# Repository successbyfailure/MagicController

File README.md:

# Magic Controller
wide range wled controllers

## Cargador de librerias
Carga las referencias LCSC de un csv con campo LCSC y descarga con easyeda2kicad todas las librerias en easyeda-libs
  
  python3 easyeda2kicad_from_csv.py componentes.csv

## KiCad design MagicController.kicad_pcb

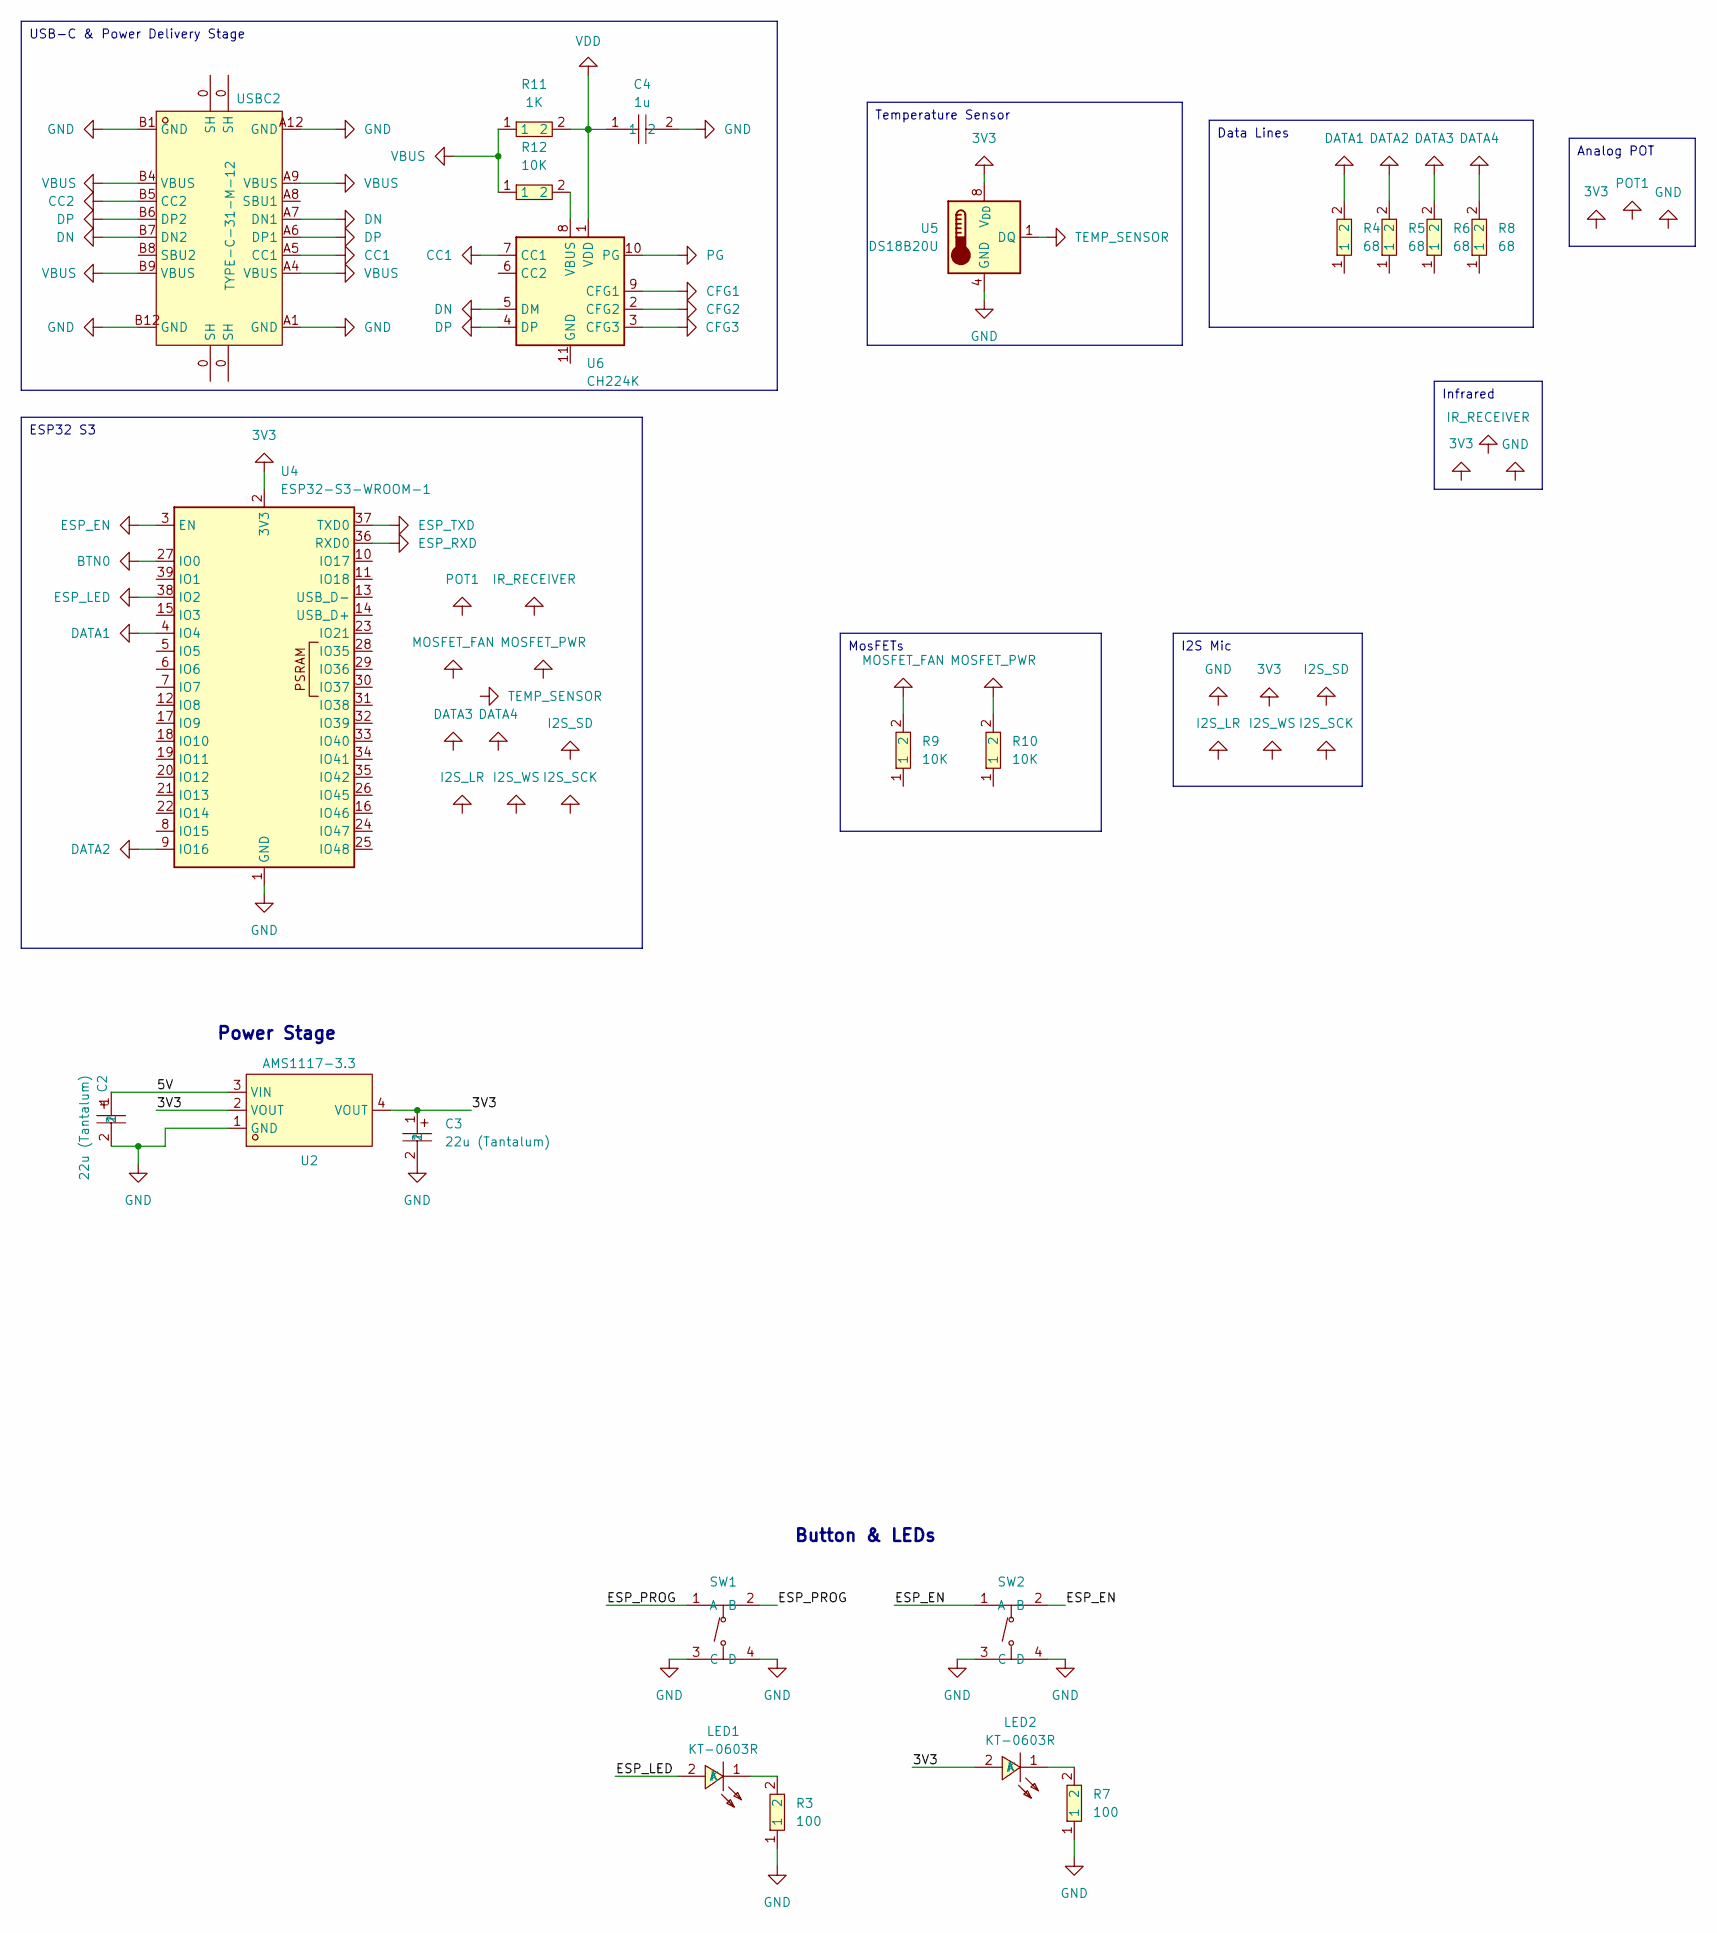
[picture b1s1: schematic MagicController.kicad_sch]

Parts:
C2, C3: 22u (Tantalum); CASE-A_3216; LCSC Part C129272
C4: 1u; C0603; LCSC Part C14663
LED1, LED2: KT-0603R; LED0603-RD; LCSC Part C2286
R3, R7: 100; R0603; LCSC Part C22775
R4, R5, R6, R8: 68; R0603; LCSC Part C22775
R9, R10, R12: 10K; R0603; LCSC Part C22775
R11: 1K; R0603; LCSC Part C22775
SW1, SW2: TS-1187A-B-A-B; SW-SMD_4P-L5.1-W5.1-P3.70-LS6.5-TL_H1.5; LCSC Part C318884
U2: AMS1117-3.3; SOT-223-3_L6.5-W3.4-P2.30-LS7.0-BR; LCSC Part C6186
U4: ESP32-S3-WROOM-1; ESP32-S3-WROOM-2
U5: DS18B20U; MSOP-8_3x3mm_P0.65mm
U6: CH224K; SSOP-10-1EP_3.9x4.9mm_P1mm_EP2.1x3.3mm_ThermalVias
USBC2: TYPE-C-31-M-12; USB-C_SMD-TYPE-C-31-M-12; LCSC Part C165948

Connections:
3V3: C3.1, LED2.2 (A), U2.2 (VOUT), U2.4 (VOUT), U4.2 (3V3), U5.8 (V_{DD})
/5V: C2.1, U2.3 (VIN)
/ESP_PROG: SW1.1 (A), SW1.2 (B)
BTN0: U4.27 (IO0)
CC1: U6.7 (CC1), USBC2.A5 (CC1)
CC2: USBC2.B5 (CC2)
CFG1: U6.9 (CFG1)
CFG2: U6.2 (CFG2)
CFG3: U6.3 (CFG3)
DATA1: R4.2, U4.4 (IO4)
DATA2: R5.2, U4.9 (IO16)
DATA3: R6.2
DATA4: R8.2
DN: U6.5 (DM), USBC2.A7 (DN1), USBC2.B7 (DN2)
DP: U6.4 (DP), USBC2.A6 (DP1), USBC2.B6 (DP2)
ESP_EN: SW2.1 (A), SW2.2 (B), U4.3 (EN)
ESP_LED: LED1.2 (A), U4.38 (IO2)
ESP_RXD: U4.36 (RXD0)
ESP_TXD: U4.37 (TXD0)
GND: C2.2, C3.2, C4.2, R3.1, R7.1, SW1.3 (C), SW1.4 (D), SW2.3 (C), SW2.4 (D), U2.1 (GND), U4.1 (GND), U4.40 (GND), U4.41 (GND), U5.4 (GND), USBC2.A1 (GND), USBC2.A12 (GND), USBC2.B1 (GND), USBC2.B12 (GND)
MOSFET_FAN: R9.2
MOSFET_PWR: R10.2
unnamed: LED1.1 (K), R3.2
unnamed: LED2.1 (K), R7.2
unnamed: R12.2, U6.8 (VBUS)
PG: U6.10 (PG)
TEMP_SENSOR: U5.1 (DQ)
VBUS: R11.1, R12.1, USBC2.A4 (VBUS), USBC2.A9 (VBUS), USBC2.B4 (VBUS), USBC2.B9 (VBUS)
VDD: C4.1, R11.2, U6.1 (VDD)

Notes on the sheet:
ESP32 S3
Analog POT
I2S Mic
MosFETs
Infrared
Temperature Sensor
Data Lines
USB-C & Power Delivery Stage
Power Stage
Button & LEDs

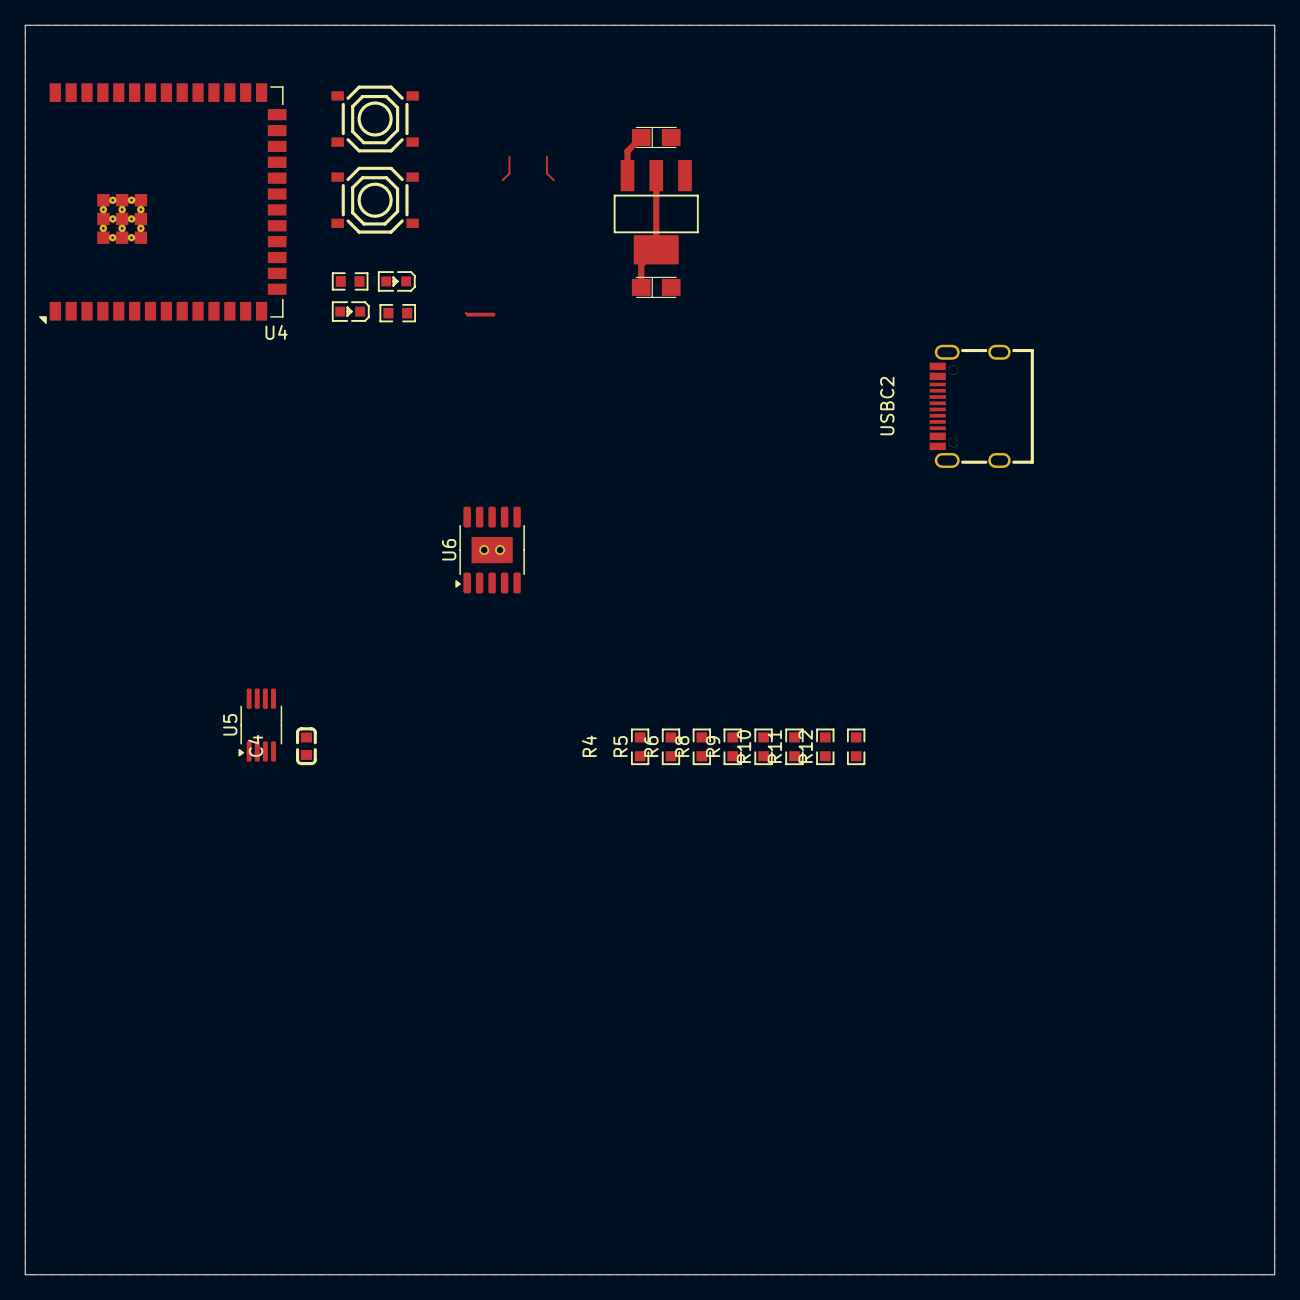
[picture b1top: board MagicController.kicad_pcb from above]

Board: 2 copper layers, 100.0 x 100.0 mm, 22 parts (0 on the bottom side), 16 nets.

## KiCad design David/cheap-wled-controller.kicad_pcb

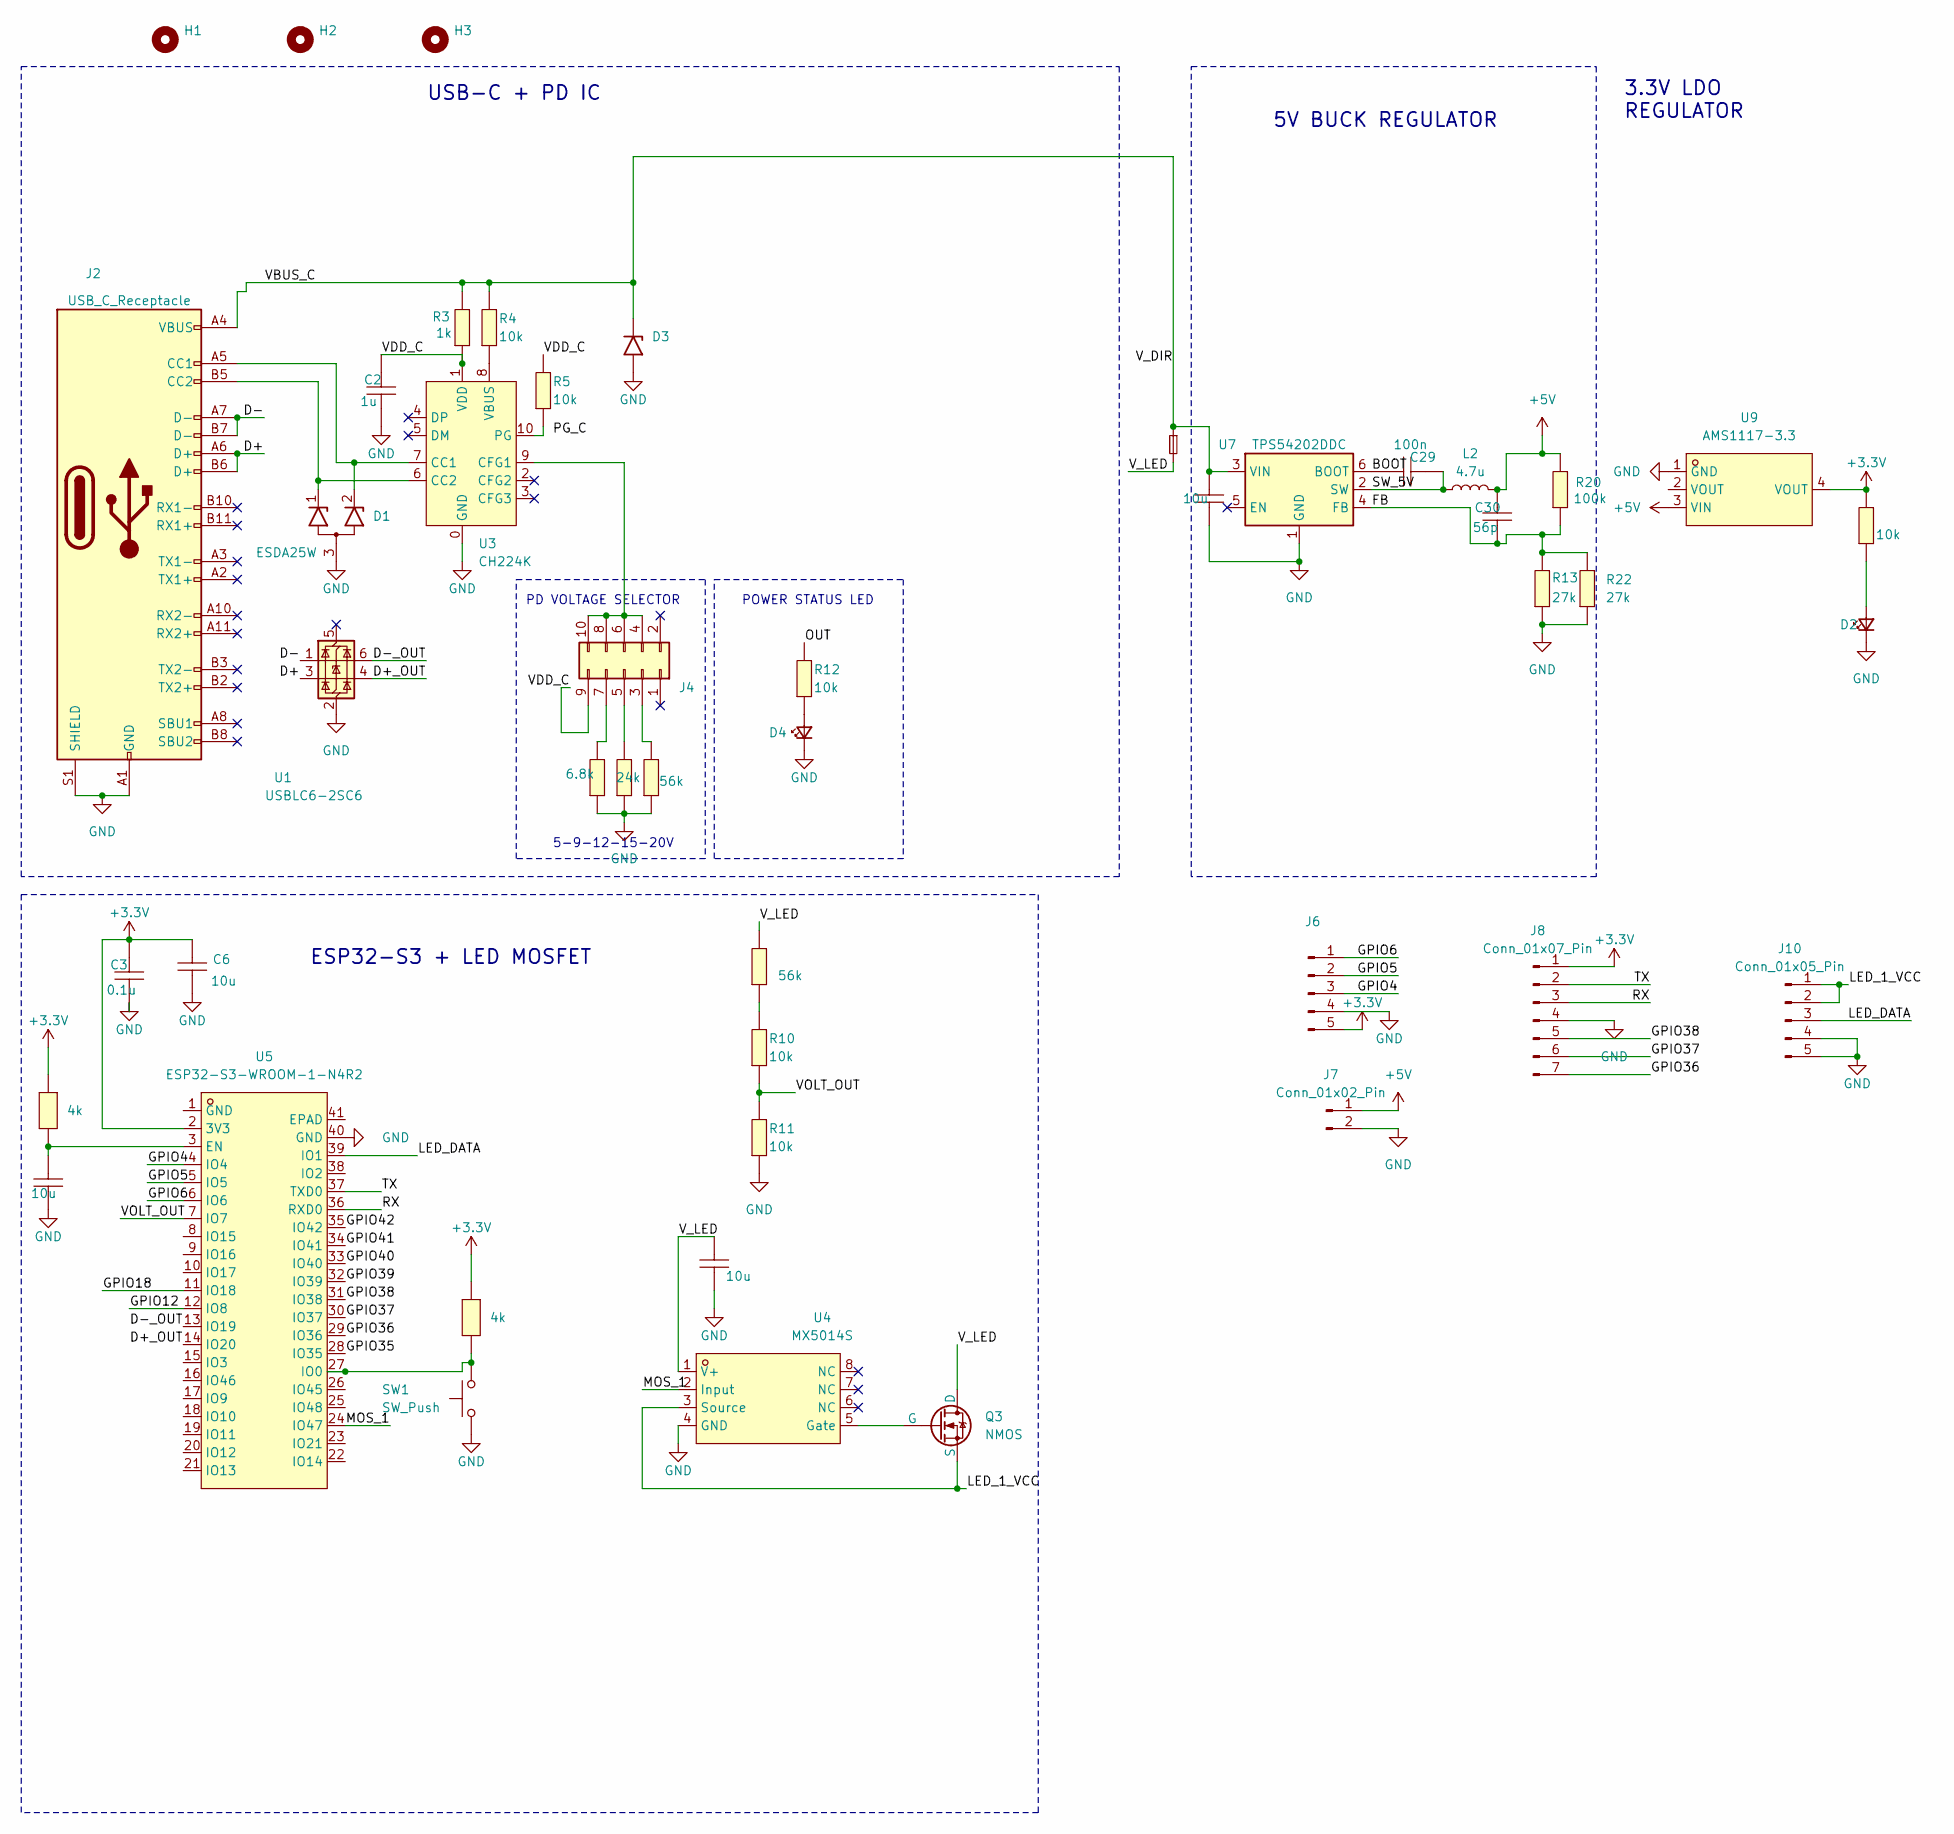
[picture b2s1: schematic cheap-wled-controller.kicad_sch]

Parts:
C1, C5, C6, C7: 10u; C0805; LCSC Part C1713
C2: 1u; C0805; LCSC Part C215803
C3: 0.1u; C0805; LCSC Part C476766
C29: 100n; C0805; LCSC Part C476766
C30: 56p; C0805; LCSC Part C1828
D1: ESDA25W; SOT-323_SC-70; LCSC C3021136
D2: LED_Small; LED0805-R-RD; LCSC C5123548
D3: D_SMA; LCSC C383698
D4: LED_Small; LED0805-R-RD; LCSC C965799
F2: DIR; FUSE-TH_XF-508P-A-B; LCSC C19727304
H1, H2, H3: MountingHole_3.2mm_M3
J2: USB_C_Receptacle; USB-C_SMD-TYPE-C-31-M-12; LCSC C165948
J4: Conn_02x05_Odd_Even; PinHeader_2x05_P2.00mm_Vertical; LCSC C7501288
J6: Conn_01x05_Pin; PinSocket_1x05_P2.54mm_Vertical
J7: Conn_01x02_Pin; JST_PH_B2B-PH-K_1x02_P2.00mm_Vertical; LCSC C131337
J8: Conn_01x07_Pin; PinSocket_1x07_P2.54mm_Vertical
J10: Conn_01x05_Pin; CONN-TH_5P-P3.81_KF124-3.81-5P; LCSC C72336
L2: 4.7u; L_1008_2520Metric; LCSC C91237
Q3: NMOS; DFN-8_L5.9-W5.2-P1.27-LS6.2-BL; LCSC C919580
R2, R15: 56k; R0805; LCSC Part C17756
R3: 1k; R0805; LCSC Part C17513
R4, R5, R10, R11, R12, R14: 10k; R0805; LCSC Part C17414
R6, R7: 4k; R0805; LCSC Part C2828855
R13, R22: 27k; R0805; LCSC Part C114533
R16: 24k; R0805; LCSC Part C17575
R17: 6.8k; R0805; LCSC Part C17772
R20: 100k; R0805; LCSC Part C149504
SW1: SW_Push; SW-SMD_TSA245G00D-250; LCSC C2846758
U1: USBLC6-2SC6; SOT-23-6; LCSC C2827654
U3: CH224K; ESSOP-10_L4.9-W3.9-P1.0-LS6.0-TL-EP; LCSC C970725
U4: MX5014S; SOIC-8_L4.9-W3.9-P1.27-LS6.0-BL; LCSC Part C5359091
U5: ESP32-S3-WROOM-1-N4R2; WIRELM-SMD_ESP32-S3-WROOM-1; LCSC Part C2913203
U7: TPS54202DDC; SOT-23-6; LCSC C191884
U9: AMS1117-3.3; SOT-223-3_L6.5-W3.4-P2.30-LS7.0-BR; LCSC Part C6186

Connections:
+3.3V: C3.2, C6.2, J6.5, J8.1, R6.1, R7.1, R14.2, U5.2 (3V3), U9.4 (VOUT)
+5V: C30.2, J7.1, L2.2, R20.2, U9.3 (VIN)
/BOOT: C29.2, U7.6 (BOOT)
/D+: J2.A6 (D+), J2.B6 (D+), U1.3 (I/O2)
/D+_OUT: U1.4 (I/O2), U5.14 (IO20)
/D-: J2.A7 (D-), J2.B7 (D-), U1.1 (I/O1)
/D-_OUT: U1.6 (I/O1), U5.13 (IO19)
/FB: C30.1, R13.2, R20.1, R22.2, U7.4 (FB)
/GPIO4: J6.3, U5.4 (IO4)
/GPIO5: J6.2, U5.5 (IO5)
/GPIO6: J6.1, U5.6 (IO6)
/GPIO12: U5.12 (IO8)
/GPIO18: U5.11 (IO18)
/GPIO35: U5.28 (IO35)
/GPIO36: J8.7, U5.29 (IO36)
/GPIO37: J8.6, U5.30 (IO37)
/GPIO38: J8.5, U5.31 (IO38)
/GPIO39: U5.32 (IO39)
/GPIO40: U5.33 (IO40)
/GPIO41: U5.34 (IO41)
/GPIO42: U5.35 (IO42)
/LED_1_VCC: J10.1, J10.2, Q3.3 (S), U4.3 (Source)
/LED_DATA: J10.3, U5.39 (IO1)
/MOS_1: U4.2 (Input), U5.24 (IO47)
/OUT: R12.2
/RX: J8.3, U5.36 (RXD0)
/SW_5V: C29.1, L2.1, U7.2 (SW)
/TX: J8.2, U5.37 (TXD0)
/VBUS_C: C5.2, D3.1 (A1), F2.1, J2.A4 (VBUS), J2.A9 (VBUS), J2.B4 (VBUS), J2.B9 (VBUS), R3.2, R4.2, U7.3 (VIN)
/VDD_C: C2.2, J4.9, R3.1, R5.2, U3.1 (VDD)
/VOLT_OUT: R10.1, R11.2, U5.7 (IO7)
/V_LED: C1.2, F2.2, Q3.2 (D), R15.2, U4.1 (V+)
GND: C1.1, C2.1, C3.1, C5.1, C6.1, C7.1, D1.3 (A), D2.1 (K), D3.2 (A2), D4.1 (K), J2.A1 (GND), J2.A12 (GND), J2.B1 (GND), J2.B12 (GND), J2.S1 (SHIELD), J6.4, J7.2, J8.4, J10.4, J10.5, R2.1, R11.1, R13.1, R16.1, R17.1, R22.1, SW1.1, U1.2 (GND), U3.0 (GND), U4.4 (GND), U5.40 (GND), U7.1 (GND), U9.1 (GND)
unnamed: D1.1 (K1), J2.B5 (CC2), U3.6 (CC2)
unnamed: D1.2 (K2), J2.A5 (CC1), U3.7 (CC1)
unnamed: D2.2 (A), R14.1
unnamed: D4.2 (A), R12.1
unnamed: J4.3, R2.2
unnamed: J4.5, R16.2
unnamed: J4.7, R17.2
unnamed: J4.4, J4.6, J4.8, J4.10, U3.9 (CFG1)
unnamed: Q3.1 (G), U4.5 (Gate)
unnamed: R10.2, R15.1
unnamed: R5.1, U3.10 (PG)
unnamed: R4.1, U3.8 (VBUS)
unnamed: C7.2, R6.2, U5.3 (EN)
unnamed: R7.2, SW1.2, U5.27 (IO0)

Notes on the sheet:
ESP32-S3 + LED MOSFET
USB-C + PD IC
POWER STATUS LED
5V BUCK REGULATOR
5-9-12-15-20V
PD VOLTAGE SELECTOR
3.3V LDO REGULATOR

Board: 2 copper layers, 47 parts (1 on the bottom side), 39 nets, no tracks yet.

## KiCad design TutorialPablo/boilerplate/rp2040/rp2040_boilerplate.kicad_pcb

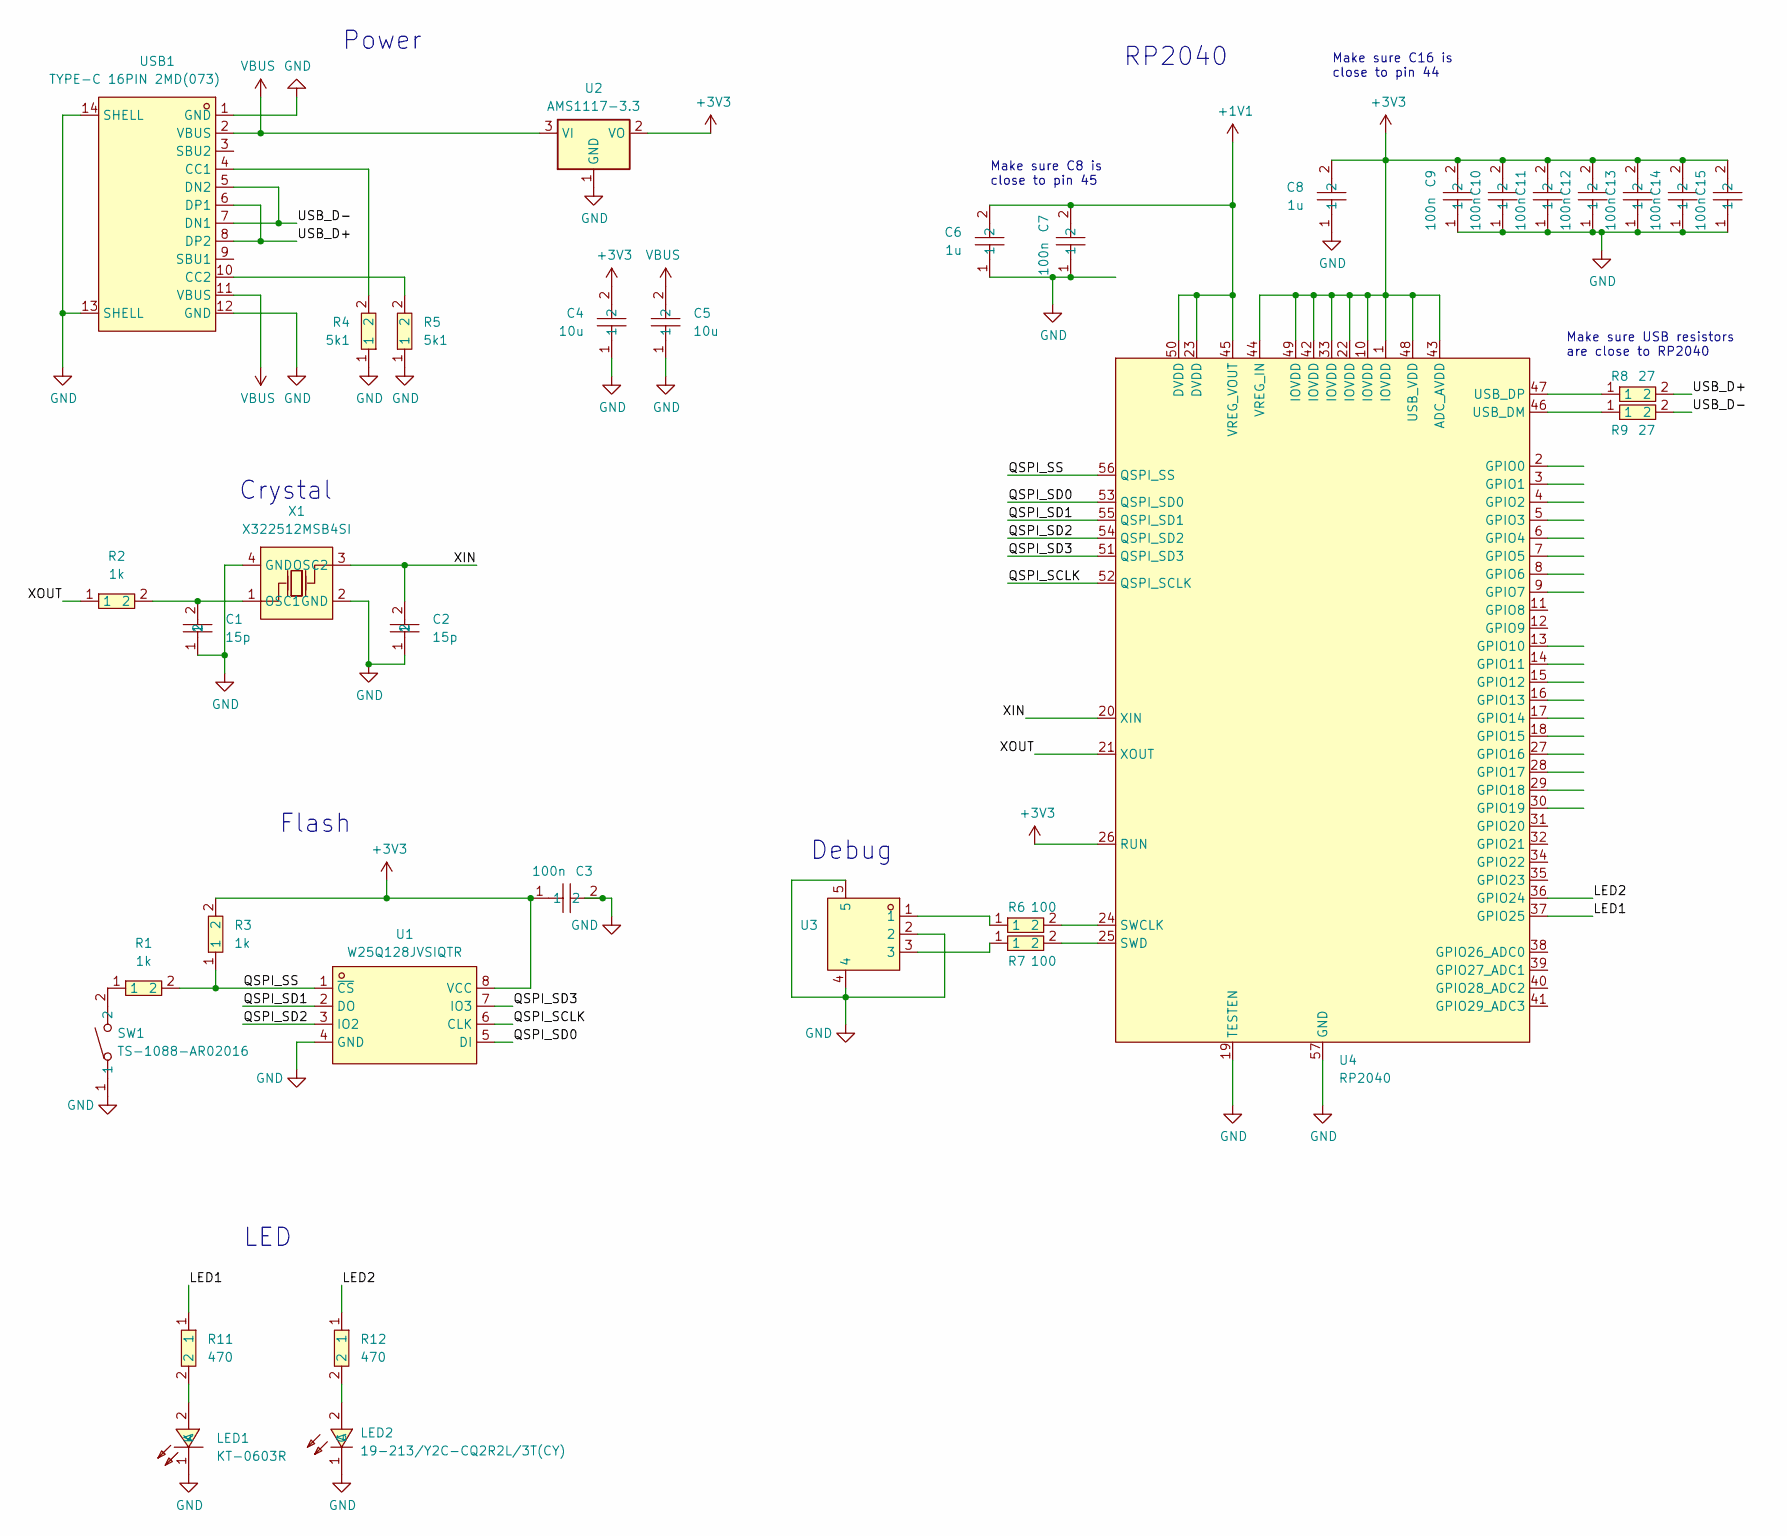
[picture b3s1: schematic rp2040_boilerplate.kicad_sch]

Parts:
C1, C2: 15p; C0603; LCSC Part C1644
C3, C7, C9, C10, C11, C12, C13, C14, C15: 100n; C0402; LCSC Part C1525
C4, C5: 10u; C0805; LCSC Part C15850
C6, C8: 1u; C0603; LCSC Part C15849
LED1: KT-0603R; LED0603-RD; LCSC Part C2286
LED2: 19-213/Y2C-CQ2R2L/3T(CY); LED0603-RD-YELLOW; LCSC Part C72038
R1, R2, R3: 1k; R0603; LCSC Part C21190
R4, R5: 5k1; R0603; LCSC Part C23186
R6, R7: 100; R0603; LCSC Part C22775
R8, R9: 27; R0805; LCSC Part C17594
R11, R12: 470; R0402; LCSC Part C25117
SW1: TS-1088-AR02016; SW-SMD_L3.9-W3.0-P4.45; LCSC Part C720477
U1: W25Q128JVSIQTR; SOIC-8_L5.3-W5.3-P1.27-LS8.0-BL; LCSC Part C97521
U2: AMS1117-3.3; SOT-223-3_TabPin2
U3: SM03B-SRSS-TB(LF)(SN)(P); CONN-SMD_SM03B-SRSS-TB-LF-SN-P; LCSC Part C160403
U4: RP2040; LQFN-56_L7.0-W7.0-P0.4-EP; LCSC Part C2040
USB1: TYPE-C 16PIN 2MD(073); USB-C-SMD_TYPE-C-6PIN-2MD-073; LCSC Part C2765186
X1: X322512MSB4SI; CRYSTAL-SMD_4P-L3.2-W2.5-BL; LCSC Part C9002

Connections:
+1V1: C6.2, C7.2, U4.23 (DVDD), U4.45 (VREG_VOUT), U4.50 (DVDD)
+3V3: C3.1, C4.2, C8.2, C9.2, C10.2, C11.2, C12.2, C13.2, C14.2, C15.2, R3.2, U1.8 (VCC), U2.2 (VO), U4.1 (IOVDD), U4.10 (IOVDD), U4.22 (IOVDD), U4.26 (RUN), U4.33 (IOVDD), U4.42 (IOVDD), U4.43 (ADC_AVDD), U4.44 (VREG_IN), U4.48 (USB_VDD), U4.49 (IOVDD)
/LED1: R11.1, U4.37 (GPIO25)
/LED2: R12.1, U4.36 (GPIO24)
/QSPI_SCLK: U1.6 (CLK), U4.52 (QSPI_SCLK)
/QSPI_SD0: U1.5 (DI), U4.53 (QSPI_SD0)
/QSPI_SD1: U1.2 (DO), U4.55 (QSPI_SD1)
/QSPI_SD2: U1.3 (IO2), U4.54 (QSPI_SD2)
/QSPI_SD3: U1.7 (IO3), U4.51 (QSPI_SD3)
/QSPI_SS: R1.2, R3.1, U1.1 (~CS), U4.56 (QSPI_SS)
/USB_D+: R8.2, USB1.6 (DP1), USB1.8 (DP2)
/USB_D-: R9.2, USB1.5 (DN2), USB1.7 (DN1)
/XIN: C2.2, U4.20 (XIN), X1.3 (OSC2)
/XOUT: R2.1, U4.21 (XOUT)
GND: C1.1, C2.1, C3.2, C4.1, C5.1, C6.1, C7.1, C8.1, C9.1, C10.1, C11.1, C12.1, C13.1, C14.1, C15.1, LED1.1 (K), LED2.1 (C), R4.1, R5.1, SW1.1, U1.4 (GND), U2.1 (GND), U3.2, U3.4, U3.5, U4.19 (TESTEN), U4.57 (GND), USB1.1 (GND), USB1.12 (GND), USB1.13 (SHELL), USB1.14 (SHELL), X1.2 (GND), X1.4 (GND)
unnamed: LED1.2 (A), R11.2
unnamed: LED2.2 (A), R12.2
unnamed: R1.1, SW1.2
unnamed: R6.1, U3.1
unnamed: R7.1, U3.3
unnamed: R6.2, U4.24 (SWCLK)
unnamed: R7.2, U4.25 (SWD)
unnamed: R9.1, U4.46 (USB_DM)
unnamed: R8.1, U4.47 (USB_DP)
unnamed: R4.2, USB1.4 (CC1)
unnamed: R5.2, USB1.10 (CC2)
unnamed: C1.2, R2.2, X1.1 (OSC1)
VBUS: C5.2, U2.3 (VI), USB1.2 (VBUS), USB1.11 (VBUS)

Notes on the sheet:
Power
Flash
Crystal
Make sure C16 is close to pin 44
Make sure C8 is close to pin 45
Make sure USB resistors are close to RP2040
RP2040
Debug
LED

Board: 2 copper layers, 35 parts (0 on the bottom side), 28 nets, no tracks yet.

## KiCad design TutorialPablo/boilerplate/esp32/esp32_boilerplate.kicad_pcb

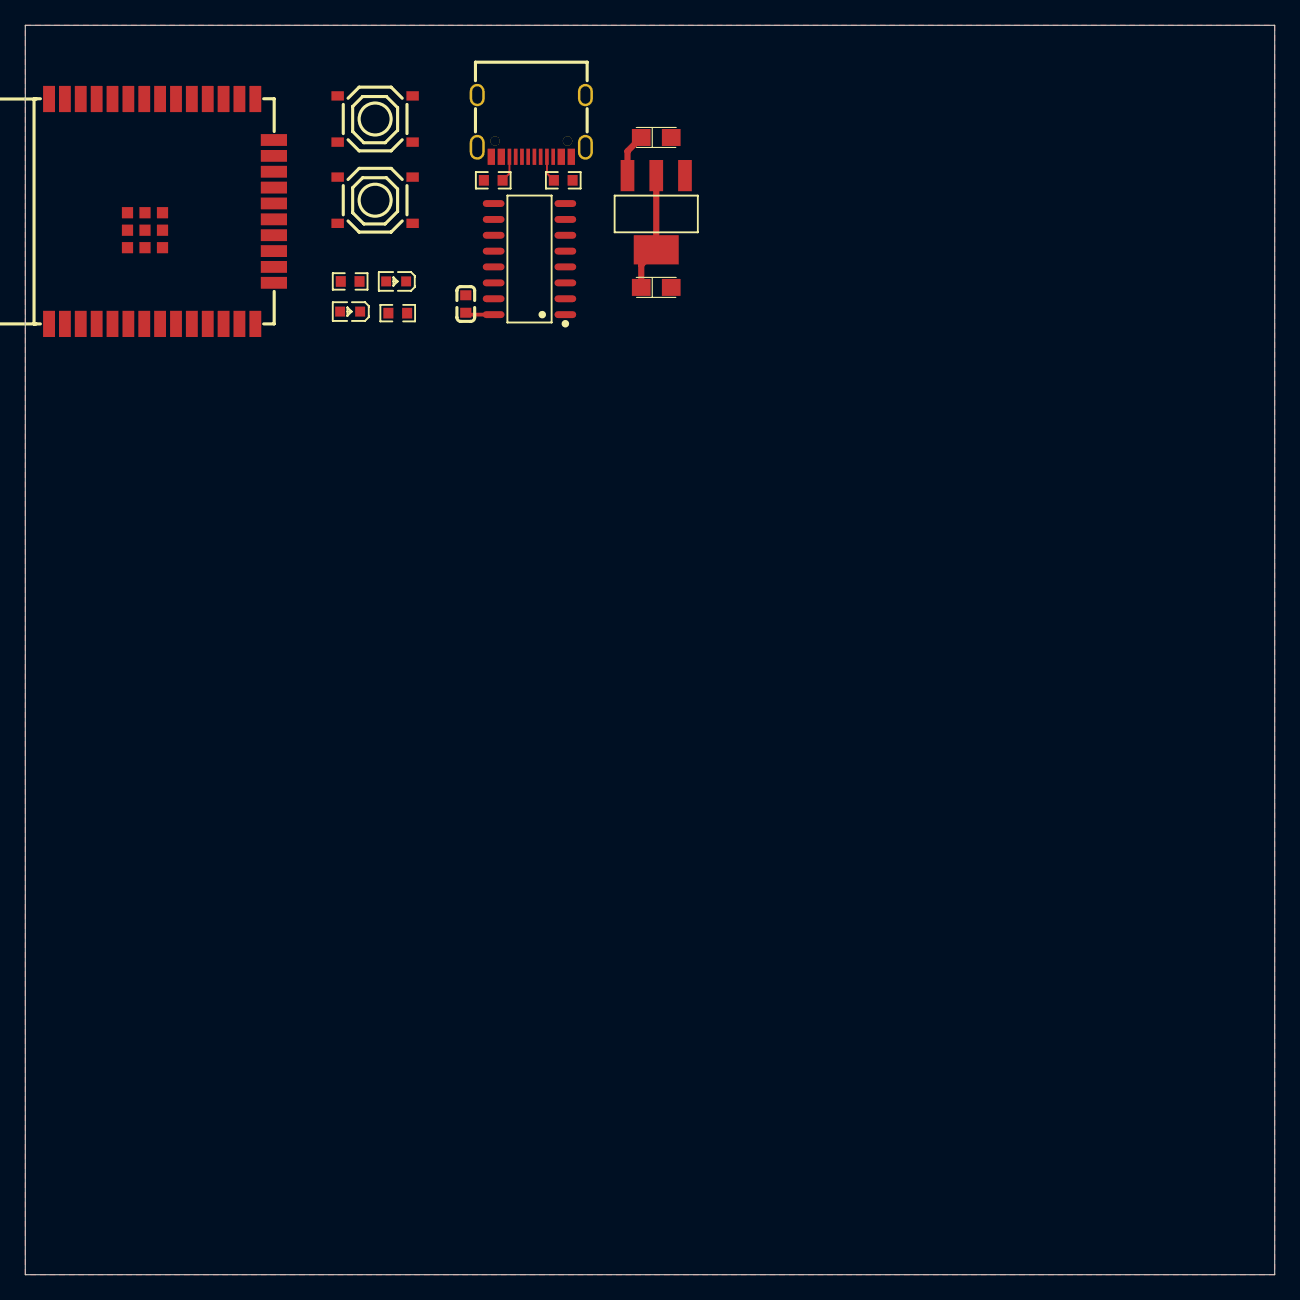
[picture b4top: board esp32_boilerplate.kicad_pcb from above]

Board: 2 copper layers, 100.0 x 100.0 mm, 15 parts (0 on the bottom side), 14 nets.

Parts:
C1: 0.1u; C0603
C2, C3: 22u (Tantalum); CASE-A_3216
LED1, LED2: KT-0603R; LED0603-RD
R1, R2: 5k1; R0603
R3, R7: 100; R0603
SW1, SW2: TS-1187A-B-A-B; SW-SMD_4P-L5.1-W5.1-P3.70-LS6.5-TL_H1.5
U1: CH340C_C7464026; SOP-16_L10.0-W3.9-P1.27-LS6.0-BL
U2: AMS1117-3.3; SOT-223-3_L6.5-W3.4-P2.30-LS7.0-BR
U3: ESP32-WROOM-32E(8MB); WIFI-SMD_ESP32-WROOM-32E
USBC1: TYPE-C-31-M-12; USB-C_SMD-TYPE-C-31-M-12

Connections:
/3V3: C1.2, C3.1, LED2.2 (A), U1.4 (V3), U1.16 (VCC), U2.2 (VOUT), U2.4 (VOUT), U3.2 (3V3)
/5V: C2.1, U2.3 (VIN), USBC1.A4 (VBUS), USBC1.A9 (VBUS), USBC1.B4 (VBUS), USBC1.B9 (VBUS)
/ESP_EN: SW2.1 (A), SW2.2 (B), U3.3 (EN)
/ESP_LED: LED1.2 (A), U3.24 (IO2)
/ESP_PROG: SW1.1 (A), SW1.2 (B), U3.25 (IO0)
/ESP_RXD: U1.2 (TXD), U3.34 (RXD0)
/ESP_TXD: U1.3 (RXD), U3.35 (TXD0)
/USB_N: U1.6 (UD-), USBC1.A7 (DN1), USBC1.B7 (DN2)
/USB_P: U1.5 (UD+), USBC1.A6 (DP1), USBC1.B6 (DP2)
GND: C1.1, C2.2, C3.2, R1.1, R2.1, R3.1, R7.1, SW1.3 (C), SW1.4 (D), SW2.3 (C), SW2.4 (D), U1.1 (GND), U2.1 (GND), U3.1 (GND), U3.15 (GND), U3.38 (GND), U3.39 (GND), USBC1.0 (SH), USBC1.A1 (GND), USBC1.A12 (GND), USBC1.B1 (GND), USBC1.B12 (GND)
unnamed: LED1.1 (K), R3.2
unnamed: LED2.1 (K), R7.2
unnamed: R2.2, USBC1.A5 (CC1)
unnamed: R1.2, USBC1.B5 (CC2)

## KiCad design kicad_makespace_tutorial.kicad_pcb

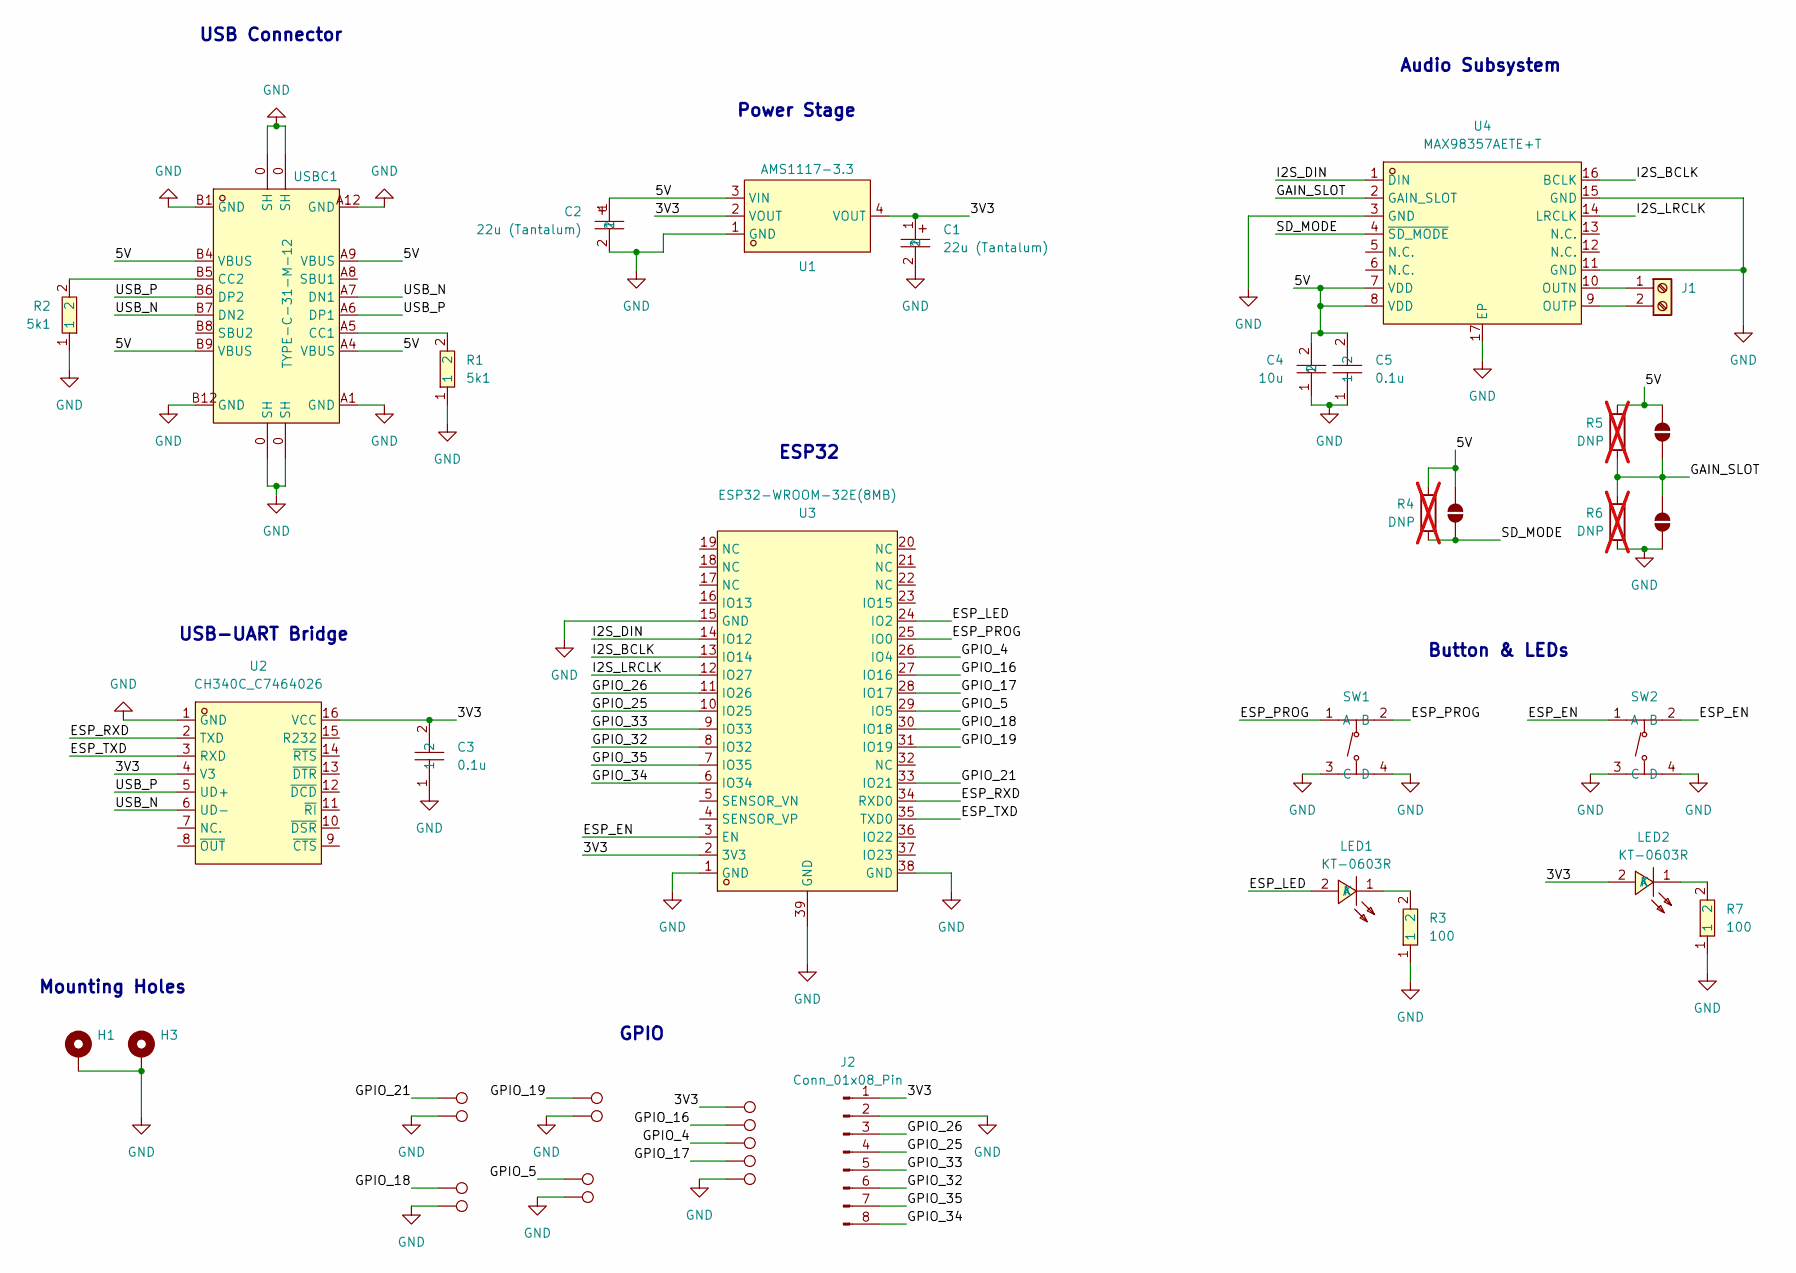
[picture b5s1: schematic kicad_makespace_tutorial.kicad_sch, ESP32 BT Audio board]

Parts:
C1, C2: 22u (Tantalum); CASE-A_3216; LCSC Part C129272
C3, C5: 0.1u; C0603; LCSC Part C14663
C4: 10u; C1206; LCSC Part C13585
H1, H3: MountingHole_Pad_MP; MountingHole_2.7mm_M2.5_DIN965_Pad
J1: Screw_Terminal_01x02; CONN-TH_2P-P5.00_WJ128V-5.0-2P
J2: Conn_01x08_Pin; PinHeader_1x08_P1.27mm_Vertical_SMD_Pin1Right
JP1, JP2, JP3: SolderJumper_2_Open; SolderJumper-2_P1.3mm_Open_TrianglePad1.0x1.5mm
LED1, LED2: KT-0603R; LED0603-RD; LCSC Part C2286
R1, R2: 5k1; R0603; LCSC Part C23186
R3, R7: 100; R0603; LCSC Part C22775
R4, R5, R6: DNP; R_0805_2012Metric_Pad1.20x1.40mm_HandSolder; not fitted
SW1, SW2: TS-1187A-B-A-B; SW-SMD_4P-L5.1-W5.1-P3.70-LS6.5-TL_H1.5; LCSC Part C318884
TP1, TP2, TP3, TP4, TP5, TP6, TP7, TP8, TP9, TP10, TP11, TP12, TP13: TestPoint; TestPoint_Pad_D1.0mm
U1: AMS1117-3.3; SOT-223-3_L6.5-W3.4-P2.30-LS7.0-BR; LCSC Part C6186
U2: CH340C_C7464026; SOP-16_L10.0-W3.9-P1.27-LS6.0-BL; LCSC Part C7464026
U3: ESP32-WROOM-32E(8MB); WIFI-SMD_ESP32-WROOM-32E; LCSC Part C701342
U4: MAX98357AETE+T; TQFN-16_L3.0-W3.0-P0.50-BL-EP1.5; LCSC Part C910544
USBC1: TYPE-C-31-M-12; USB-C_SMD-TYPE-C-31-M-12; LCSC Part C165948

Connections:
/3V3: C1.1, C3.2, J2.1, LED2.2 (A), TP7.1, U1.2 (VOUT), U1.4 (VOUT), U2.4 (V3), U2.16 (VCC), U3.2 (3V3)
/5V: C2.1, C4.2, C5.2, JP1.2 (B), JP3.2 (B), R4.1, R5.1, U1.3 (VIN), U4.7 (VDD), U4.8 (VDD), USBC1.A4 (VBUS), USBC1.A9 (VBUS), USBC1.B4 (VBUS), USBC1.B9 (VBUS)
/ESP_EN: SW2.1 (A), SW2.2 (B), U3.3 (EN)
/ESP_LED: LED1.2 (A), U3.24 (IO2)
/ESP_PROG: SW1.1 (A), SW1.2 (B), U3.25 (IO0)
/ESP_RXD: U2.2 (TXD), U3.34 (RXD0)
/ESP_TXD: U2.3 (RXD), U3.35 (TXD0)
/GAIN_SLOT: JP2.2 (B), JP3.1 (A), R5.2, R6.1, U4.2 (GAIN_SLOT)
/GPIO_4: TP9.1, U3.26 (IO4)
/GPIO_5: TP12.1, U3.29 (IO5)
/GPIO_16: TP8.1, U3.27 (IO16)
/GPIO_17: TP10.1, U3.28 (IO17)
/GPIO_18: TP5.1, U3.30 (IO18)
/GPIO_19: TP3.1, U3.31 (IO19)
/GPIO_21: TP2.1, U3.33 (IO21)
/GPIO_25: J2.4, U3.10 (IO25)
/GPIO_26: J2.3, U3.11 (IO26)
/GPIO_32: J2.6, U3.8 (IO32)
/GPIO_33: J2.5, U3.9 (IO33)
/GPIO_34: J2.8, U3.6 (IO34)
/GPIO_35: J2.7, U3.7 (IO35)
/I2S_BCLK: U3.13 (IO14), U4.16 (BCLK)
/I2S_DIN: U3.14 (IO12), U4.1 (DIN)
/I2S_LRCLK: U3.12 (IO27), U4.14 (LRCLK)
/SD_MODE: JP1.1 (A), R4.2, U4.4 (~SD_MODE)
/USB_N: U2.6 (UD-), USBC1.A7 (DN1), USBC1.B7 (DN2)
/USB_P: U2.5 (UD+), USBC1.A6 (DP1), USBC1.B6 (DP2)
GND: C1.2, C2.2, C3.1, C4.1, C5.1, H1.MP, H3.MP, J2.2, JP2.1 (A), R1.1, R2.1, R3.1, R6.2, R7.1, SW1.3 (C), SW1.4 (D), SW2.3 (C), SW2.4 (D), TP1.1, TP4.1, TP6.1, TP11.1, TP13.1, U1.1 (GND), U2.1 (GND), U3.1 (GND), U3.15 (GND), U3.38 (GND), U3.39 (GND), U4.3 (GND), U4.11 (GND), U4.15 (GND), U4.17 (EP), USBC1.0 (SH), USBC1.1, USBC1.2, USBC1.3, USBC1.A1 (GND), USBC1.A12 (GND), USBC1.B1 (GND), USBC1.B12 (GND)
unnamed: J1.1, U4.10 (OUTN)
unnamed: J1.2, U4.9 (OUTP)
unnamed: LED1.1 (K), R3.2
unnamed: LED2.1 (K), R7.2
unnamed: R1.2, USBC1.A5 (CC1)
unnamed: R2.2, USBC1.B5 (CC2)

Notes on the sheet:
Button & LEDs
Mounting Holes
Power Stage
GPIO
USB-UART Bridge
Audio Subsystem
ESP32
USB Connector
